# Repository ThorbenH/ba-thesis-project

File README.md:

# BarbelMotionTracker

This git project is dedicated to a prototype implementation that attempts to track and evaluate the motion of a barbell in the gym.

## 3D-Files

Here you will find the FFF (FDM) printable files for a case for the board. All STL-files are in metric (mm). To complete the assembly you will need some additional hardware (M3 screws, rubber pad, M3 heat set inserts, 4mmx0.5mm brass tubing, 2cm wide velcro strap)

## PCB_Design

Here you will find the KiCad8.0 design files as well as the pre exported gerbers (ready to order at JLCPCB). You will also find the ibom.html file which is a Interactive Bill Of Materials that you can open in any modern browser. It is of great use when doing board smd assembly.

## Software_Device

Here you will find a PlatformIO project that contains the software running on the board. It is written in C/C++ for the esp32 platform using the arduino framework.

To get started install VSCode, install the PlatformIO extension, plug in the board using the USB-C shared power and data port and make sure the board is turned on using the power switch.p

The software collects all the raw sensor data into a CSV-File for future of board processing.

Calibration modes can be selected by uncommenting preprocessor arguments in the "platformio.ini" file.

### Micro SD-Card

The sd-card has to be formatted as FAT32. FAT32 is only supported by micro-sd-cards with capacity less than 32GB.
The sd-card has to contain a settings.txt file that has to be populated. Check the "sdcard.h" code for details.
A good starting point might be this (make sure to include the empty lines at the end of the file, as the device expects these to write the BNO055 calibration to):

```
User
1
s
90.00
2.50
45.00
2.50
12.50
2.50
95.00
2.50

```

## Plot_Calibration

Contains a the python code to visualize a calibration as gathered by the device (see Software_Device).
To get the calibration matrix you can use the tool Magneto v1.2 at https://sites.google.com/view/sailboatinstruments1 .

## Post_Process_Data

First run "apply_calibration_and_split.py" to split one recording session into exercises and sets and apply the calibration. This requires a recorded session and a "cal_matrix.json" file in the subfolder "data". Make sure to set the correct file name for your recordig in "apply_calibration_and_split.py".
Next you can run "compute_orientation_and_motion.py". Make sure to set the correct target folder.

Some settings are required for these two steps. They can be set in "processing_settings.py".

All other files should contain "_thesis" in their name and where only used to create plots of the data for the thesis. Feel free to disregard these.

## Machine_Learning
To run the machine learning code you first need to create the dataset used for training and testing. The python code file "prepData.py" uses a hard coded location for the data. To generate the data required first run the Post_Process_Data pipeline. Then you can run the training in order "prepData.py" -> "train.py" -> "test.py".

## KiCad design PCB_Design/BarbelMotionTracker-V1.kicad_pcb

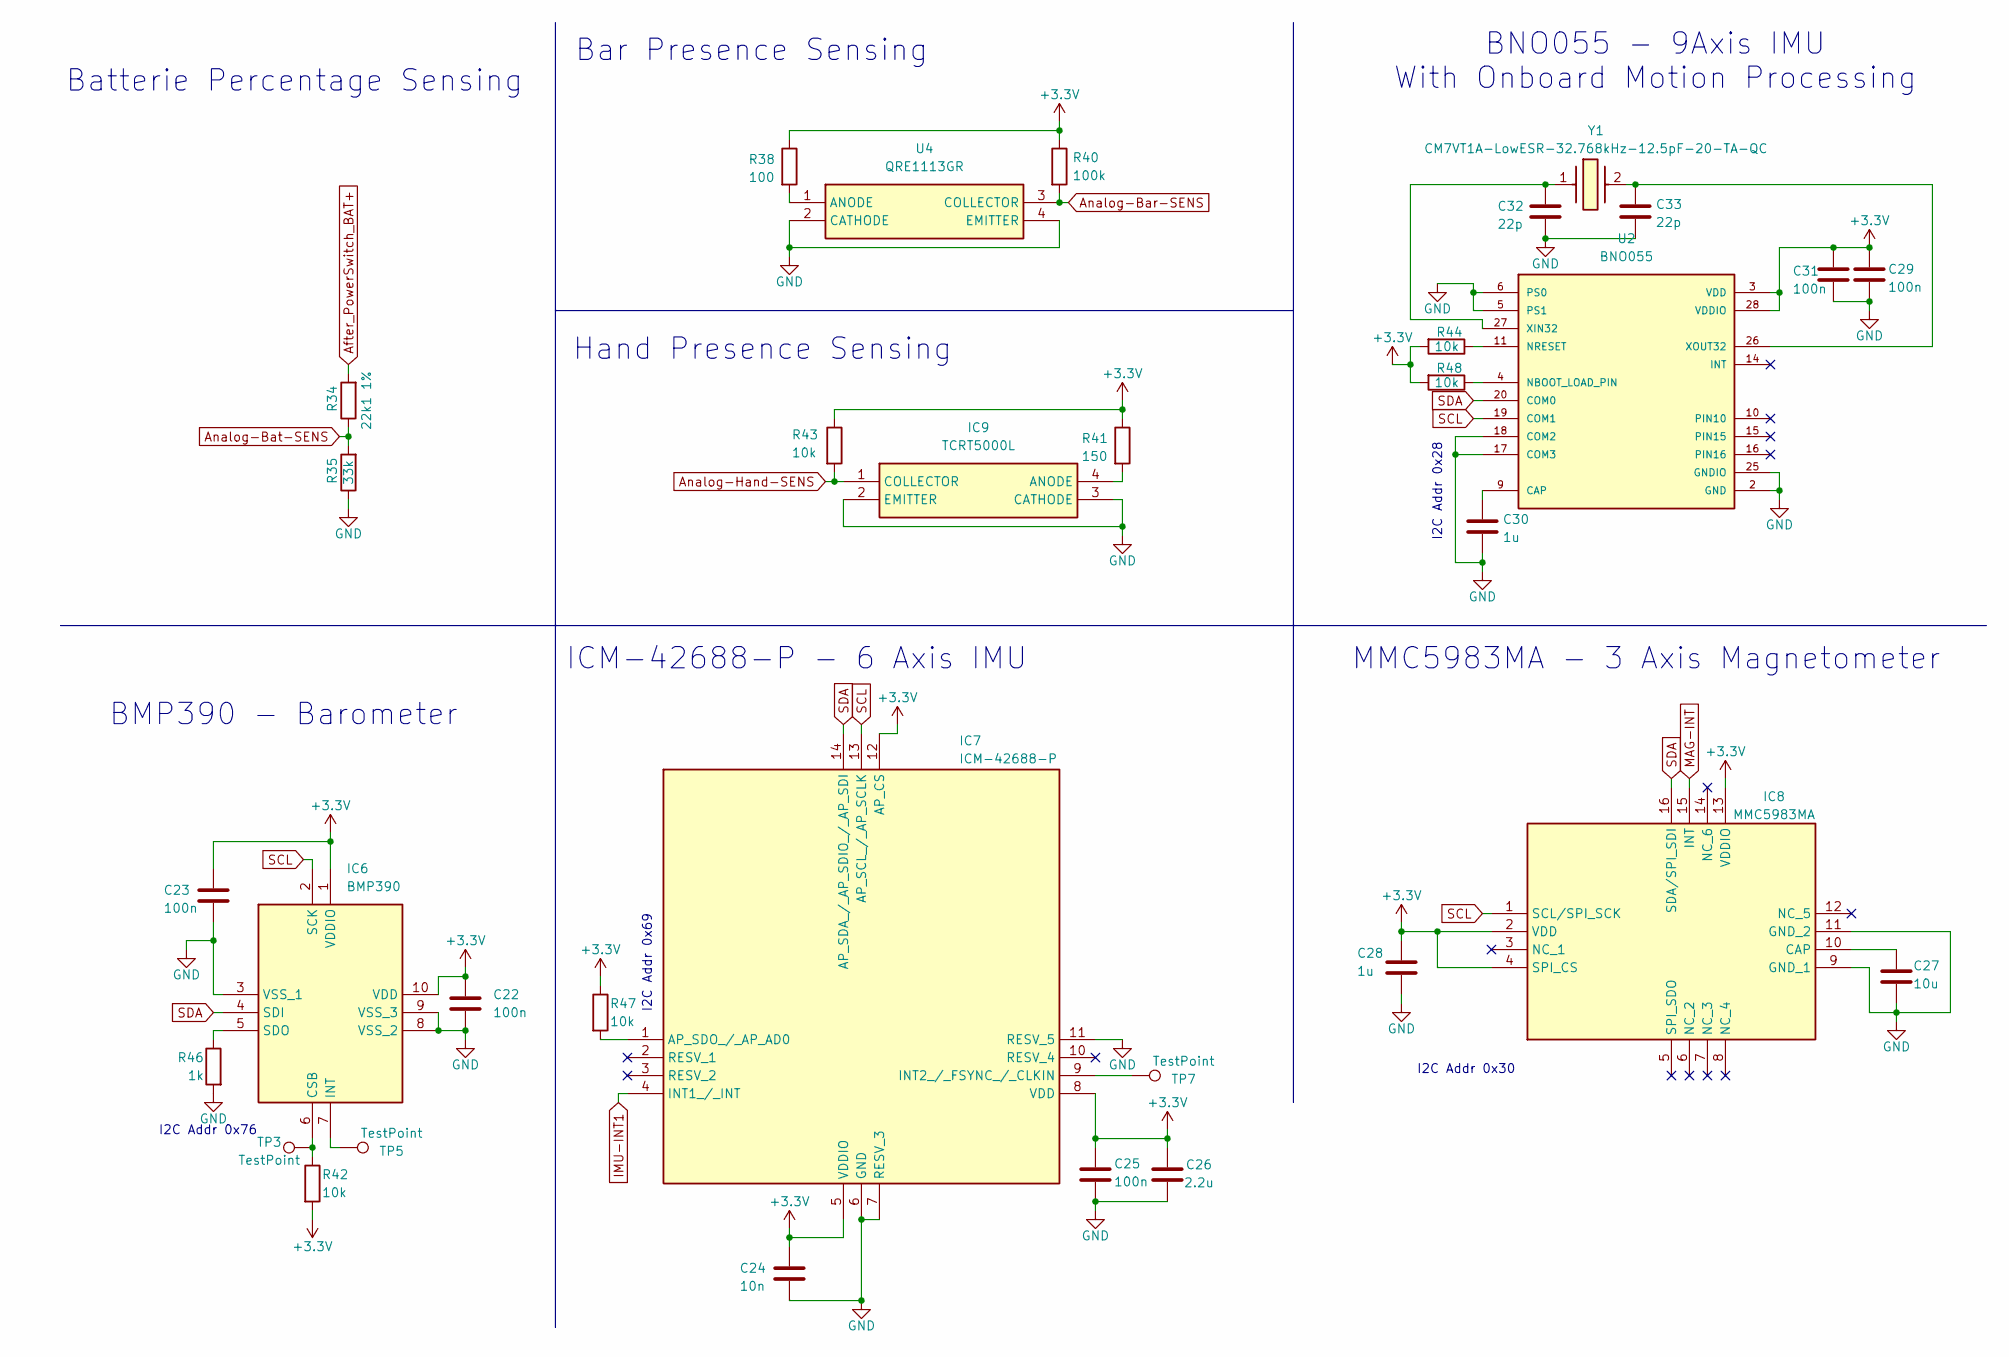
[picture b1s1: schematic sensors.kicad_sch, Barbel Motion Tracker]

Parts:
C22, C23, C25, C29, C31: 100n; C_0603_1608Metric
C24: 10n; C_0603_1608Metric
C26: 2.2u; C_0603_1608Metric
C27: 10u; C_0805_2012Metric
C28, C30: 1u; C_0603_1608Metric
C32, C33: 22p; C_0402_1005Metric
IC6: BMP390; Mouser Part Number 262-BMP390
IC7: ICM-42688-P; IIM42352; Mouser Part Number 410-ICM-42688-P
IC8: MMC5983MA; Mouser Part Number 438-MMC5983MA
IC9: TCRT5000L; Mouser Part Number 782-TCRT5000L
R34: 22k1 1%; R_0603_1608Metric
R35: 33k; R_0603_1608Metric
R38: 100; R_1206_3216Metric
R40: 100k; R_0603_1608Metric
R41: 150; R_1206_3216Metric
R42, R43, R44, R47, R48: 10k; R_0603_1608Metric
R46: 1k; R_0603_1608Metric
TP3, TP5, TP7: TestPoint; TestPoint_Pad_D1.0mm
U2: BNO055; LGA28R50P4X10_380X520X100
U4: QRE1113GR; Mouser Part Number 512-QRE1113GR
Y1: CM7VT1A-LowESR-32.768kHz-12.5pF-20-TA-QC; CM7V32768TBQA020; Mouser Part Number 428-202740-MG01

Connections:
+3.3V: C22.1, C23.1, C24.1, C25.1, C26.1, C28.1, C29.1, C31.1, IC6.1 (VDDIO), IC6.10 (VDD), IC7.5 (VDDIO), IC7.8 (VDD), IC7.12 (AP_CS), IC8.2 (VDD), IC8.4 (SPI_CS), IC8.13 (VDDIO), R38.1, R40.1, R41.1, R42.2, R43.1, R44.2, R47.1, R48.2, U2.3 (VDD), U2.28 (VDDIO); also elsewhere on the board
After_PowerSwitch_BAT+: R34.2; also elsewhere on the board
Analog-Bar-SENS: R40.2, U4.3 (COLLECTOR); also elsewhere on the board
Analog-Bat-SENS: R34.1, R35.2; also elsewhere on the board
Analog-Hand-SENS: IC9.1 (COLLECTOR), R43.2; also elsewhere on the board
GND: C22.2, C23.2, C24.2, C25.2, C26.2, C27.2, C28.2, C29.2, C30.2, C31.2, C32.2, C33.2, IC6.3 (VSS_1), IC6.8 (VSS_2), IC6.9 (VSS_3), IC7.6 (GND), IC7.7 (RESV_3), IC7.11 (RESV_5), IC8.9 (GND_1), IC8.11 (GND_2), IC9.2 (EMITTER), IC9.3 (CATHODE), R35.1, R46.2, U2.2 (GND), U2.5 (PS1), U2.6 (PS0), U2.17 (COM3), U2.18 (COM2), U2.25 (GNDIO), U4.2 (CATHODE), U4.4 (EMITTER); also elsewhere on the board
IMU-INT1: IC7.4 (INT1_/_INT); also elsewhere on the board
MAG-INT: IC8.15 (INT); also elsewhere on the board
unnamed: IC6.6 (CSB), R42.1, TP3.1
unnamed: IC6.7 (INT), TP5.1
unnamed: IC6.5 (SDO), R46.1
unnamed: IC7.1 (AP_SDO_/_AP_AD0), R47.2
unnamed: IC7.9 (INT2_/_FSYNC_/_CLKIN), TP7.1
unnamed: C27.1, IC8.10 (CAP)
unnamed: IC9.4 (ANODE), R41.2
unnamed: C30.1, U2.9 (CAP)
unnamed: R48.1, U2.4 (NBOOT_LOAD_PIN)
unnamed: R44.1, U2.11 (NRESET)
unnamed: C32.1, U2.27 (XIN32), Y1.1
unnamed: C33.1, U2.26 (XOUT32), Y1.2
unnamed: R38.2, U4.1 (ANODE)
SCL: IC6.2 (SCK), IC7.13 (AP_SCL_/_AP_SCLK), IC8.1 (SCL/SPI_SCK), U2.19 (COM1); also elsewhere on the board
SDA: IC6.4 (SDI), IC7.14 (AP_SDA_/_AP_SDIO_/_AP_SDI), IC8.16 (SDA/SPI_SDI), U2.20 (COM0); also elsewhere on the board

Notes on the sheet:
BMP390 - Barometer
I2C Addr 0x28
Batterie Percentage Sensing
ICM-42688-P - 6 Axis IMU
BNO055 - 9Axis IMU With Onboard Motion Processing
MMC5983MA - 3 Axis Magnetometer
Hand Presence Sensing
I2C Addr 0x69
I2C Addr 0x76
Bar Presence Sensing
I2C Addr 0x30

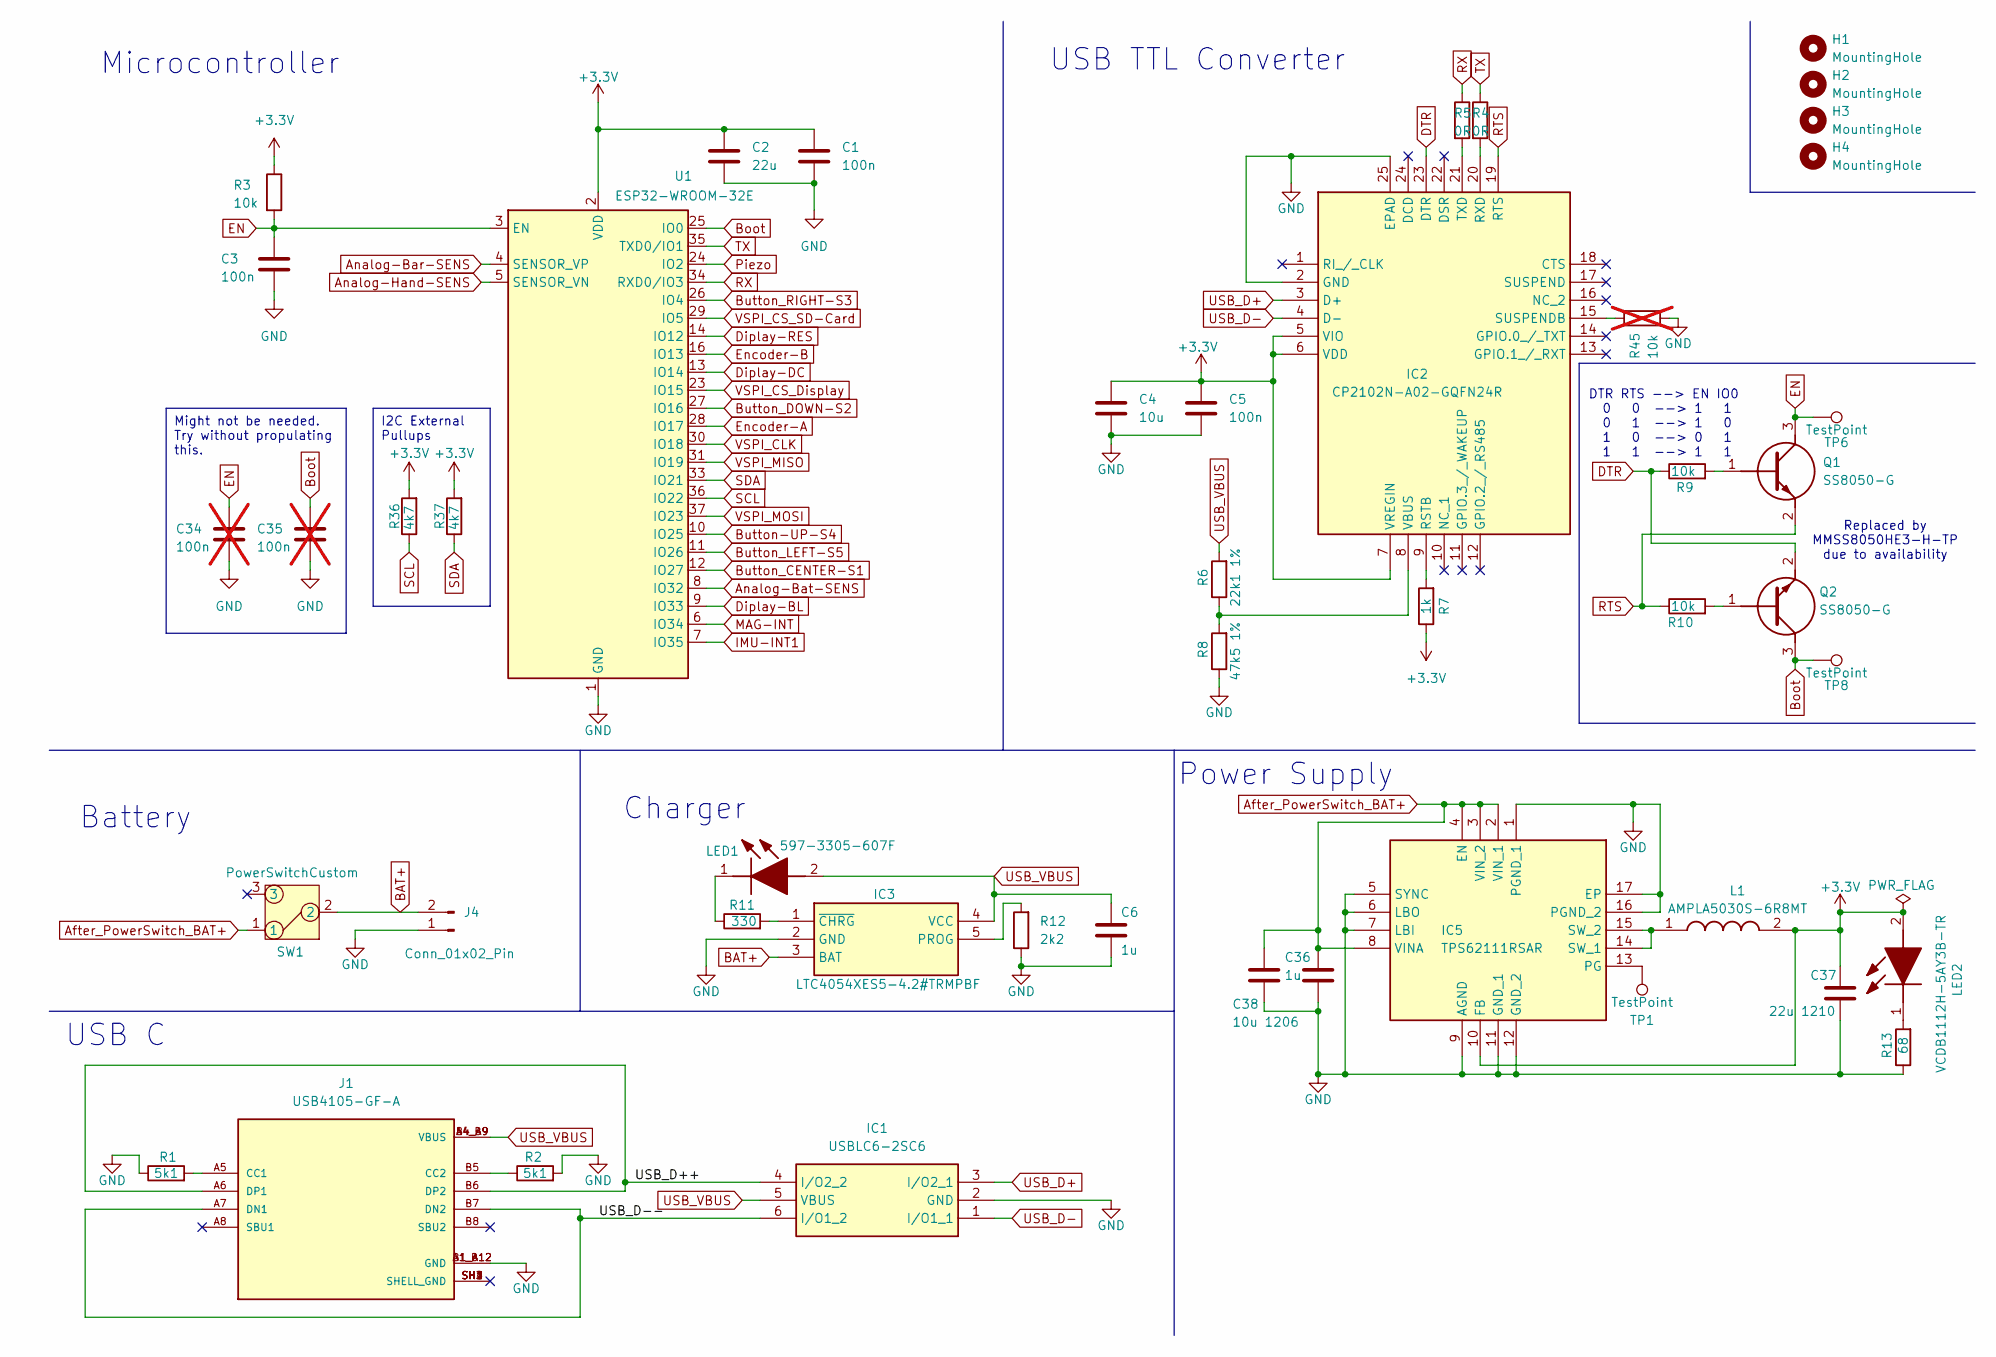
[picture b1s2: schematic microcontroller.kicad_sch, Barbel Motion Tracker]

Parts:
C1, C3, C5: 100n; C_0603_1608Metric
C2: 22u; C_0805_2012Metric
C4: 10u; C_0805_2012Metric
C6, C36: 1u; C_0603_1608Metric
C34, C35: 100n; C_0603_1608Metric; not fitted
C37: 22u 1210; C_1210_3225Metric
C38: 10u 1206; C_1206_3216Metric
H1, H2, H3, H4: MountingHole; MountingHole_2.2mm_M2
IC1: USBLC6-2SC6; SOT95P280X145-6N; Mouser Part Number 511-USBLC6-2SC6
IC2: CP2102N-A02-GQFN24R; QFN50P400X400X80-25N-D; Mouser Part Number 634-CP2102NA02QFN24R
IC3: LTC4054XES5-4.2#TRMPBF; SOT95P280X100-5N; Mouser Part Number 584-C4054XES54.2TMPF
IC5: TPS62111RSAR; QFN65P400X400X100-17N; Mouser Part Number 595-TPS62111RSAR
J1: USB4105-GF-A; GCT_USB4105-GF-A; PARTREV B3
J4: Conn_01x02_Pin; JST_PH_S2B-PH-K_1x02_P2.00mm_Horizontal
L1: AMPLA5030S-6R8MT; INDPM5752X300N; Manufacturer_Part_Number AMPLA5030S-6R8MT
LED1: 597-3305-607F; LEDC2012X70N; Mouser Part Number 645-597-3305-607F
LED2: VCDB1112H-5AY3B-TR; LEDC2012X90N; Mouser Part Number 327-VCDB1112H5AY3BTR
Q1, Q2: SS8050-G; SOT95P240X115-3N; Mouser Part Number 750-SS8050-G
R1, R2: 5k1; R_0603_1608Metric
R3, R9, R10: 10k; R_0603_1608Metric
R4, R5: 0R; R_0603_1608Metric
R6: 22k1 1%; R_0603_1608Metric
R7: 1k; R_0603_1608Metric
R8: 47k5 1%; R_0603_1608Metric
R11: 330; R_0603_1608Metric
R12: 2k2; R_0603_1608Metric
R13: 68; R_0603_1608Metric
R36, R37: 4k7; R_0603_1608Metric
R45: 10k; R_0603_1608Metric; not fitted
SW1: PowerSwitchCustom
TP1, TP6, TP8: TestPoint; TestPoint_Pad_D1.0mm
U1: ESP32-WROOM-32E

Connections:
+3.3V: C1.1, C2.1, C4.1, C5.1, C37.1, IC2.5 (VIO), IC2.6 (VDD), IC2.7 (VREGIN), IC5.10 (FB), L1.2, LED2.2 (A), R3.1, R7.1, R36.2, R37.2, U1.2 (VDD); also elsewhere on the board
/microcontroller/USB_D++: IC1.4 (I/O2_2), J1.A6 (DP1), J1.B6 (DP2)
/microcontroller/USB_D--: IC1.6 (I/O1_2), J1.A7 (DN1), J1.B7 (DN2)
After_PowerSwitch_BAT+: C36.1, C38.1, IC5.2 (VIN_1), IC5.3 (VIN_2), IC5.4 (EN), IC5.8 (VINA), SW1.1; also elsewhere on the board
Analog-Bar-SENS: U1.4 (SENSOR_VP); also elsewhere on the board
Analog-Bat-SENS: U1.8 (IO32); also elsewhere on the board
Analog-Hand-SENS: U1.5 (SENSOR_VN); also elsewhere on the board
BAT+: IC3.3 (BAT), J4.2, SW1.2
Boot: C35.1, Q2.3 (C), TP8.1, U1.25 (IO0)
Button-UP-S4: U1.10 (IO25); also elsewhere on the board
Button_CENTER-S1: U1.12 (IO27); also elsewhere on the board
Button_DOWN-S2: U1.27 (IO16); also elsewhere on the board
Button_LEFT-S5: U1.11 (IO26); also elsewhere on the board
Button_RIGHT-S3: U1.26 (IO4); also elsewhere on the board
DTR: IC2.23 (DTR), Q2.2 (E), R9.1
Diplay-BL: U1.9 (IO33); also elsewhere on the board
Diplay-DC: U1.13 (IO14); also elsewhere on the board
Diplay-RES: U1.14 (IO12); also elsewhere on the board
EN: C3.1, C34.1, Q1.3 (C), R3.2, TP6.1, U1.3 (EN)
Encoder-A: U1.28 (IO17); also elsewhere on the board
Encoder-B: U1.16 (IO13); also elsewhere on the board
GND: C1.2, C2.2, C3.2, C4.2, C5.2, C6.2, C34.2, C35.2, C36.2, C37.2, C38.2, IC1.2 (GND), IC2.2 (GND), IC2.25 (EPAD), IC3.2 (GND), IC5.1 (PGND_1), IC5.5 (SYNC), IC5.6 (LBO), IC5.7 (LBI), IC5.9 (AGND), IC5.11 (GND_1), IC5.12 (GND_2), IC5.16 (PGND_2), IC5.17 (EP), J1.A1_B12 (GND), J1.B1_A12 (GND), J4.1, R1.1, R2.2, R8.1, R12.1, R13.1, R45.2, U1.1 (GND), U1.15 (GND), U1.38 (GND), U1.39 (GND); also elsewhere on the board
IMU-INT1: U1.7 (IO35); also elsewhere on the board
MAG-INT: U1.6 (IO34); also elsewhere on the board
unnamed: IC2.9 (RSTB), R7.2
unnamed: IC2.20 (RXD), R4.2
unnamed: IC2.15 (SUSPENDB), R45.1
unnamed: IC2.21 (TXD), R5.2
unnamed: IC2.8 (VBUS), R6.1, R8.2
unnamed: IC3.5 (PROG), R12.2
unnamed: IC3.1 (~CHRG), R11.2
unnamed: IC5.13 (PG), TP1.1
unnamed: IC5.14 (SW_1), IC5.15 (SW_2), L1.1
unnamed: J1.A5 (CC1), R1.2
unnamed: J1.B5 (CC2), R2.1
unnamed: LED1.1 (K), R11.1
unnamed: LED2.1 (K), R13.2
unnamed: Q1.1 (B), R9.2
unnamed: Q2.1 (B), R10.2
Piezo: U1.24 (IO2); also elsewhere on the board
RTS: IC2.19 (RTS), Q1.2 (E), R10.1
RX: R5.1, U1.34 (RXD0/IO3)
SCL: R36.1, U1.36 (IO22); also elsewhere on the board
SDA: R37.1, U1.33 (IO21); also elsewhere on the board
TX: R4.1, U1.35 (TXD0/IO1)
USB_D+: IC1.3 (I/O2_1), IC2.3 (D+)
USB_D-: IC1.1 (I/O1_1), IC2.4 (D-)
USB_VBUS: C6.1, IC1.5 (VBUS), IC3.4 (VCC), J1.A4_B9 (VBUS), J1.B4_A9 (VBUS), LED1.2 (A), R6.2
VSPI_CLK: U1.30 (IO18); also elsewhere on the board
VSPI_CS_Display: U1.23 (IO15); also elsewhere on the board
VSPI_CS_SD-Card: U1.29 (IO5); also elsewhere on the board
VSPI_MISO: U1.31 (IO19); also elsewhere on the board
VSPI_MOSI: U1.37 (IO23); also elsewhere on the board

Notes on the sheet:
I2C External Pullups
Might not be needed. Try without propulating this.
DTR RTS --> EN IO0 0 0 --> 1 1 0 1 --> 1 0 1 0 --> 0 1 1 1 --> 1 1
USB C
Charger
USB TTL Converter
Replaced by MMSS8050HE3-H-TP due to availability
Battery
Microcontroller
Power Supply

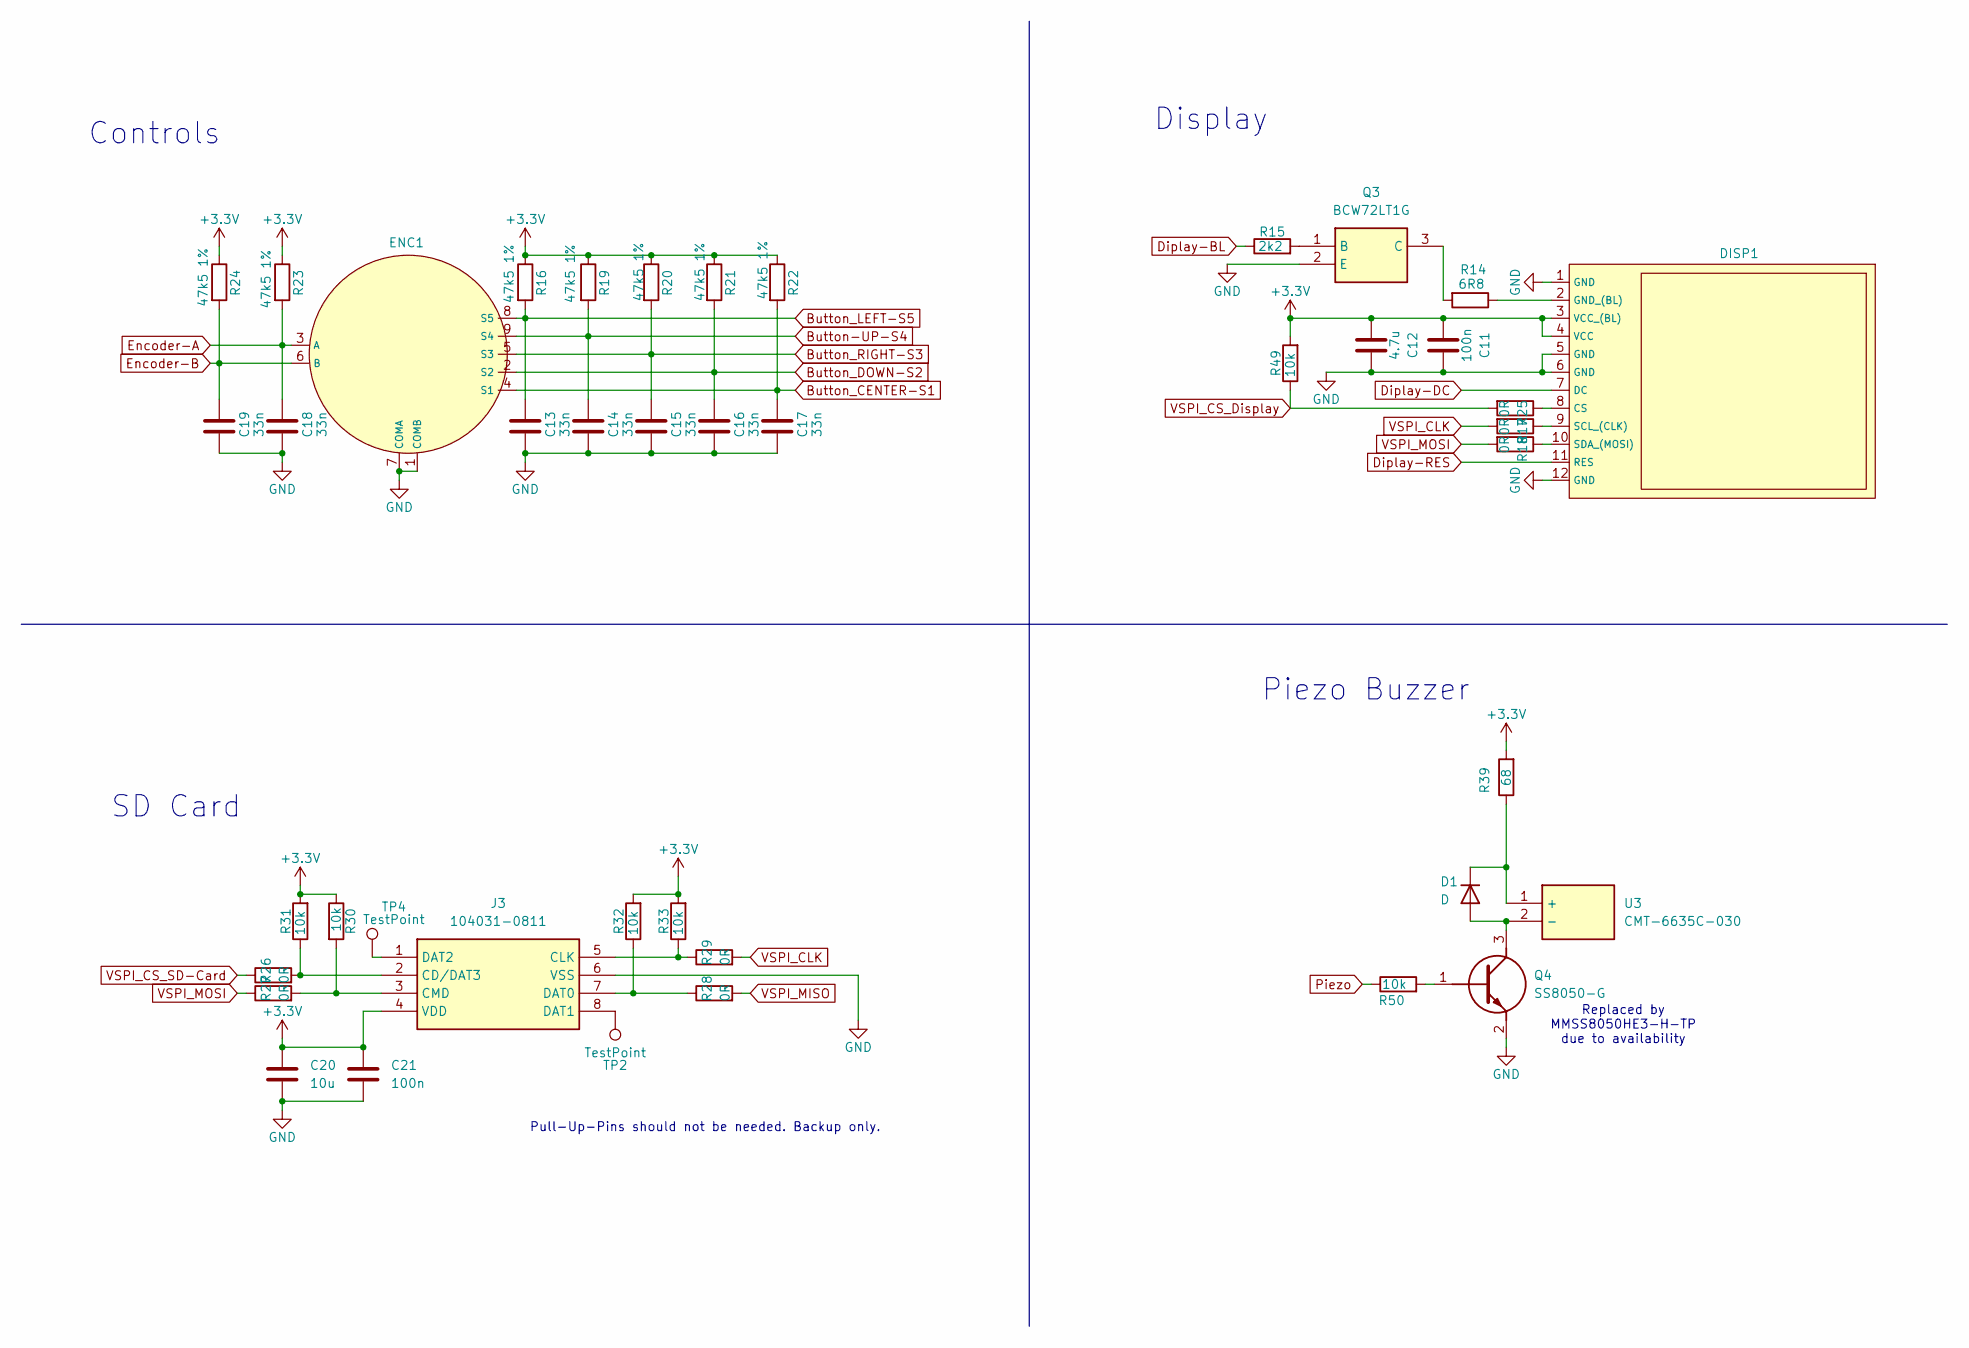
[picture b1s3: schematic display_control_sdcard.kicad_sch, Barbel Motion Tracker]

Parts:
C11, C21: 100n; C_0603_1608Metric
C12: 4.7u; C_0603_1608Metric
C13, C14, C15, C16, C17, C18, C19: 33n; C_0603_1608Metric
C20: 10u; C_0805_2012Metric
D1: D; D_0805_2012Metric
DISP1: Display_ST7789V2
ENC1: ZippyRotaryEncoder_ANO
J3: 104031-0811; 1040310811; Mouser Part Number 538-104031-0811
Q3: BCW72LT1G; SOT96P237X111-3N; Mouser Part Number 863-BCW72LT1G
Q4: SS8050-G; SOT95P240X115-3N; Mouser Part Number 750-SS8050-G
R14: 6R8; R_1206_3216Metric
R15: 2k2; R_0603_1608Metric
R16, R19, R20, R21, R22, R23, R24: 47k5 1%; R_0603_1608Metric
R17, R18, R25, R26, R27, R28, R29: 0R; R_0603_1608Metric
R30, R31, R32, R33, R49, R50: 10k; R_0603_1608Metric
R39: 68; R_0603_1608Metric
TP2, TP4: TestPoint; TestPoint_Pad_D1.0mm
U3: CMT-6635C-030; CMT6635C030; Mouser Part Number 490-CMT-6635C-030

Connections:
+3.3V: C11.1, C12.1, C20.1, C21.1, DISP1.3 (VCC_(BL)), DISP1.4 (VCC), J3.4 (VDD), R16.1, R19.1, R20.1, R21.1, R22.1, R23.1, R24.1, R30.1, R31.2, R32.2, R33.2, R39.2, R49.2; also elsewhere on the board
Button-UP-S4: C14.2, ENC1.9 (S4), R19.2; also elsewhere on the board
Button_CENTER-S1: C17.2, ENC1.4 (S1), R22.2; also elsewhere on the board
Button_DOWN-S2: C16.2, ENC1.2 (S2), R21.2; also elsewhere on the board
Button_LEFT-S5: C13.2, ENC1.8 (S5), R16.2; also elsewhere on the board
Button_RIGHT-S3: C15.2, ENC1.5 (S3), R20.2; also elsewhere on the board
Diplay-BL: R15.1; also elsewhere on the board
Diplay-DC: DISP1.7 (DC); also elsewhere on the board
Diplay-RES: DISP1.11 (RES); also elsewhere on the board
Encoder-A: C18.2, ENC1.3 (A), R23.2; also elsewhere on the board
Encoder-B: C19.2, ENC1.6 (B), R24.2; also elsewhere on the board
GND: C11.2, C12.2, C13.1, C14.1, C15.1, C16.1, C17.1, C18.1, C19.1, C20.2, C21.2, DISP1.1 (GND), DISP1.5 (GND), DISP1.6 (GND), DISP1.12 (GND), ENC1.1 (COMB), ENC1.7 (COMA), J3.6 (VSS), Q3.2 (E), Q4.2 (E); also elsewhere on the board
unnamed: D1.2 (A), Q4.3 (C), U3.2 (-)
unnamed: D1.1 (K), R39.1, U3.1 (+)
unnamed: DISP1.8 (CS), R25.1
unnamed: DISP1.2 (GND_(BL)), R14.1
unnamed: DISP1.9 (SCL_(CLK)), R17.1
unnamed: DISP1.10 (SDA_(MOSI)), R18.1
unnamed: J3.2 (CD/DAT3), R26.2, R31.1
unnamed: J3.5 (CLK), R29.1, R33.1
unnamed: J3.3 (CMD), R27.2, R30.2
unnamed: J3.7 (DAT0), R28.1, R32.1
unnamed: J3.8 (DAT1), TP2.1
unnamed: J3.1 (DAT2), TP4.1
unnamed: Q3.1 (B), R15.2
unnamed: Q3.3 (C), R14.2
unnamed: Q4.1 (B), R50.2
Piezo: R50.1; also elsewhere on the board
VSPI_CLK: R17.2, R29.2; also elsewhere on the board
VSPI_CS_Display: R25.2, R49.1; also elsewhere on the board
VSPI_CS_SD-Card: R26.1; also elsewhere on the board
VSPI_MISO: R28.2; also elsewhere on the board
VSPI_MOSI: R18.2, R27.1; also elsewhere on the board

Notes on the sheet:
Pull-Up-Pins should not be needed. Backup only.
Piezo Buzzer
Display
Controls
SD Card
Replaced by MMSS8050HE3-H-TP due to availability

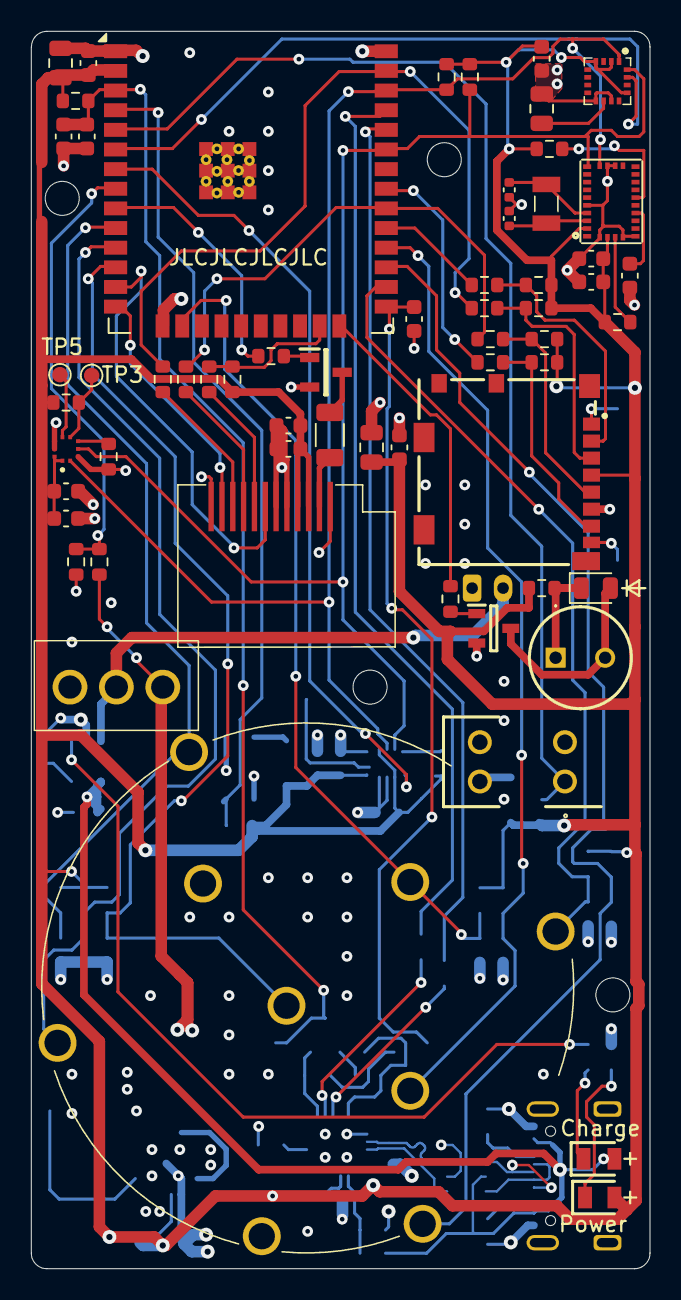
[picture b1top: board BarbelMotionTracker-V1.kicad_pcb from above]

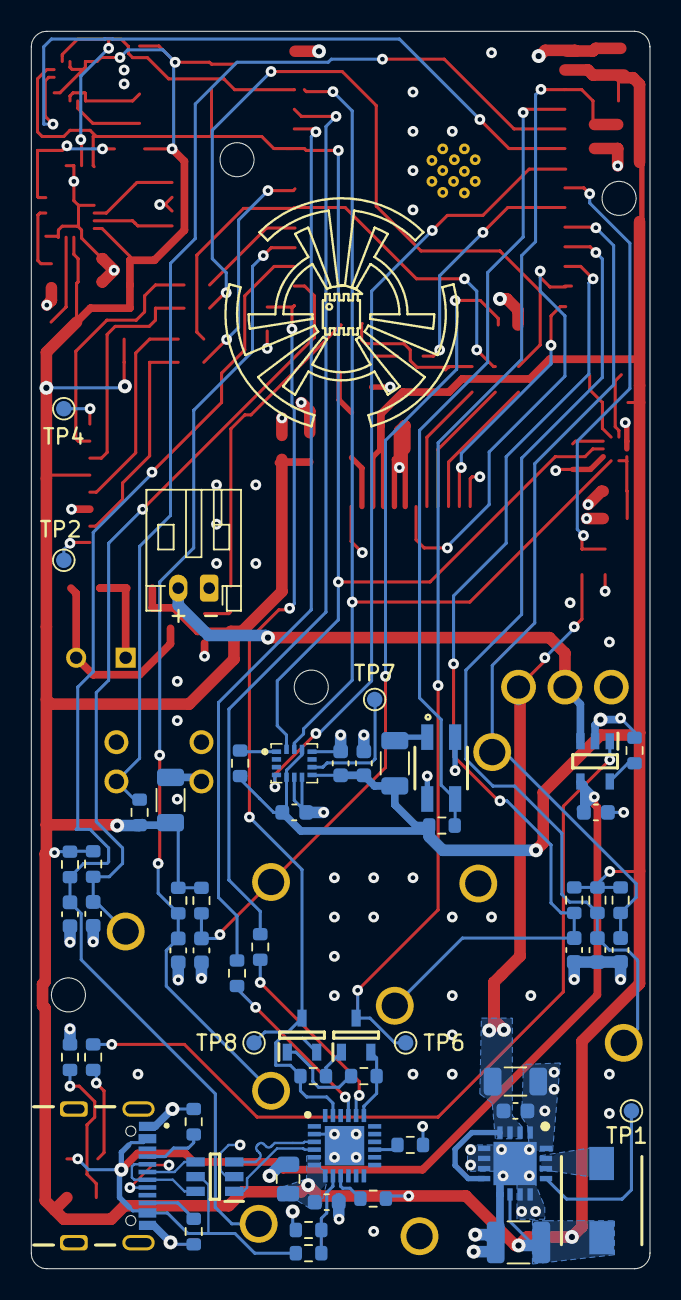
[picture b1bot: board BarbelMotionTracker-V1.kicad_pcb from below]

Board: 4 copper layers, 40.0 x 80.0 mm, 123 parts (58 on the bottom side), 81 nets.

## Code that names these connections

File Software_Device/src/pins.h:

#pragma once

static const int BOOT_PIN            = 0;
static const int TX_PIN              = 1;
static const int RX_PIN              = 3;
static const int SDA_PIN             = 21;
static const int SCL_PIN             = 22;



static const int PIEZO               = 2;
static const int BUTTON_CENTER_S1    = 27;
static const int BUTTON_DOWN_S2      = 16;
static const int BUTTON_RIGHT_S3     = 4;
static const int BUTTON_UP_S4        = 25;
static const int BUTTON_LEFT_S5      = 26;
static const int ENCODER_A           = 17;
static const int ENCODER_B           = 13;



static const int VSPI_CLK            = 18;
static const int VSPI_MISO           = 19;
static const int VSPI_MOSI           = 23;

static const int DISPLAY_RES         = 12;
static const int DISPLAY_DC          = 14;
static const int DISPLAY_BL          = 33;
static const int VSPI_CS_DISPLAY     = 15;

static const int VSPI_CS_SD_CARD     = 5;



static const int MAG_INT             = 34;
static const int IMU_INT1            = 35;



static const int ANALOG_BAT_SENS     = 32;       
static const int ANALOG_BAR_SENS     = 36; //SENSOR_VP
static const int ANALOG_HAND_SENS    = 39; //SENSOR_VN

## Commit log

2024-11-03 Final Project
2024-11-03 Update README.md, fixed typo
